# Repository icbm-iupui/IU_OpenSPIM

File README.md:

12/6/16. Additions by Indiana University, Indiana Center for Biological Microscopy
Seth Winfree completed 2015.

This repo contains the IU-OpenSPIM additions made to support NEOS AOTF control 
and filterwheel control on the emission from within the plugin.  These are supported
in the multiview acquisition tab and via a new DAC slider control for setting AOTF
transmission and filterwheel position.

This repo was orginally forked in 2015 with the intention of pulling it back to
the master but in the time I forked it and made my changes, significant changes
were made to the master making it difficult to merge.  Thus, for now, this is record
of the changes that could be implemented in the current OpenSPIM plugin to 
support an AOTF and FW from within the plugin.  

# Original README

The [OpenSPIM](http://openspim.org/) project is a collaboration between multiple
labs to establish an accessible, easily adjustable light sheet microscope
system.

The *SPIMAcquisition* plugin for [Micro Manager](https://micro-manager.org) is
the primary means to acquire image stacks with the OpenSPIM setups.

# How to build

To build this plugin, two extra steps are required before letting Maven (or
any Integrated Development Environment with a Maven integration) build the
project: The Micro-Manager artifacts need to be installed locally because they
are not available via any public Maven repository yet.

Assuming that you already have a nightly build (e.g. by following the
[Micro-Manager-dev update site](http://sites.imagej.net/Micro-Manager-dev/)),
install the artifacts into your local Maven repository by executing the
following two commands inside the `ImageJ.app/` directory containing
Micro-Manager:

```bash
cd plugins/Micro-Manager
mvn install:install-file -DgroupId=org.micromanager -Dversion=1.4.21-SNAPSHOT \
	-Dpackaging=jar -DartifactId=MMJ_ -Dfile=MMJ_.jar
mvn install:install-file -DgroupId=org.micromanager -Dversion=1.4.21-SNAPSHOT \
	-Dpackaging=jar -DartifactId=MMCoreJ -Dfile=MMCoreJ.jar
```

After that, a simple `mvn -Dscijava.enforce.skip` will build the
`SPIMAcquisition` plugin which can then be installed by copying
`target/SPIMAcquisition-<version>.jar` into `Fiji.app/mmplugins/`.

# Installing into a Micro-Manager directory instead of Fiji

The SPIMAcquisition plugin depends on a couple of components that are shipped
with Fiji but not with Micro-Manager. Therefore, you will have to work a little
harder if you want to install the plugin into a vanilla Micro-Manager as
downloaded from [the Micro-Manager website](https://micro-manager.org):

1. Run `mvn dependency:copy-dependencies` in the SPIMAcquisition directory
2. From `target/dependency/` in that subdirectory, copy the `imglib2-*.jar` files to your Micro-Manager's `mmplugins/` subdirectory.
3. Copy `target/SPIMAcquisition-1.0.0-SNAPSHOT.jar` to the `mmplugins/` subdirectory, too.
4. Restart Micro-Manager.

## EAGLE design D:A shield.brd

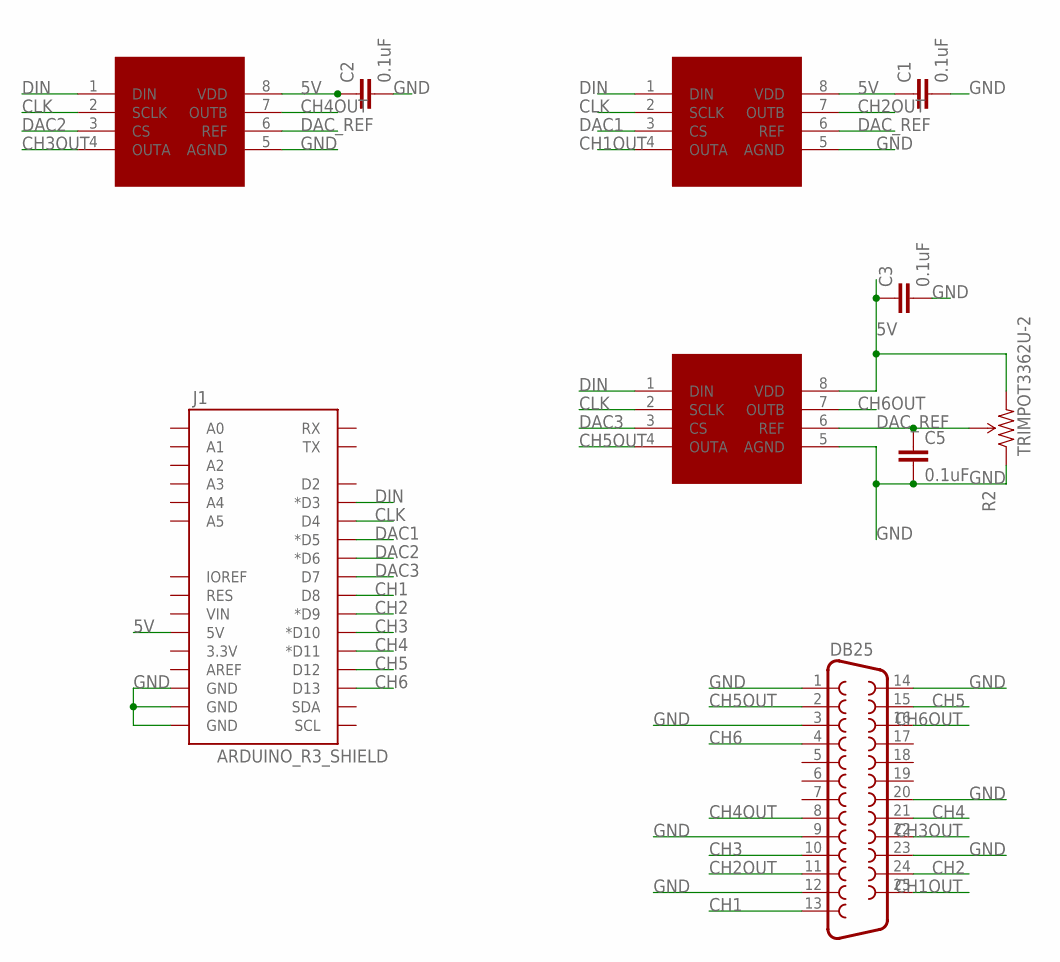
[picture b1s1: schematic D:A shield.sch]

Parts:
C1, C2, C3, C5: 0.1uF; 1206
DAC1, DAC2, DAC3: TLV5618; DIL08
DB25: F25HP
J1: ARDUINO_R3_SHIELD; UNO_R3_SHIELD
R2: TRIMPOT3362U-2; 3362U-2

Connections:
5V: C1.1, C2.1, C3.1, DAC1.8 (VDD), DAC2.8 (VDD), DAC3.8 (VDD), J1.5V, R2.3 (CW)
CH1: DB25.13, J1.D8
CH1OUT: DAC1.4 (OUTA), DB25.25
CH2: DB25.24, J1.D9 (*D9)
CH2OUT: DAC1.7 (OUTB), DB25.11
CH3: DB25.10, J1.D10 (*D10)
CH3OUT: DAC3.4 (OUTA), DB25.22
CH4: DB25.21, J1.D11 (*D11)
CH4OUT: DAC3.7 (OUTB), DB25.8
CH5: DB25.15, J1.D12
CH5OUT: DAC2.4 (OUTA), DB25.2
CH6: DB25.4, J1.D13
CH6OUT: DAC2.7 (OUTB), DB25.16
CLK: DAC1.2 (SCLK), DAC2.2 (SCLK), DAC3.2 (SCLK), J1.D4
DAC1: DAC1.3 (CS), J1.D5 (*D5)
DAC2: DAC3.3 (CS), J1.D6 (*D6)
DAC3: DAC2.3 (CS), J1.D7
DAC_REF: C5.1, DAC1.6 (REF), DAC2.6 (REF), DAC3.6 (REF), R2.2 (WIPER)
DIN: DAC1.1 (DIN), DAC2.1 (DIN), DAC3.1 (DIN), J1.D3 (*D3)
GND: C1.2, C2.2, C3.2, C5.2, DAC1.5 (AGND), DAC2.5 (AGND), DAC3.5 (AGND), DB25.1, DB25.3, DB25.9, DB25.12, DB25.14, DB25.20, DB25.23, J1.GND@0 (GND), J1.GND@1 (GND), J1.GND@2 (GND), R2.1 (CCW)

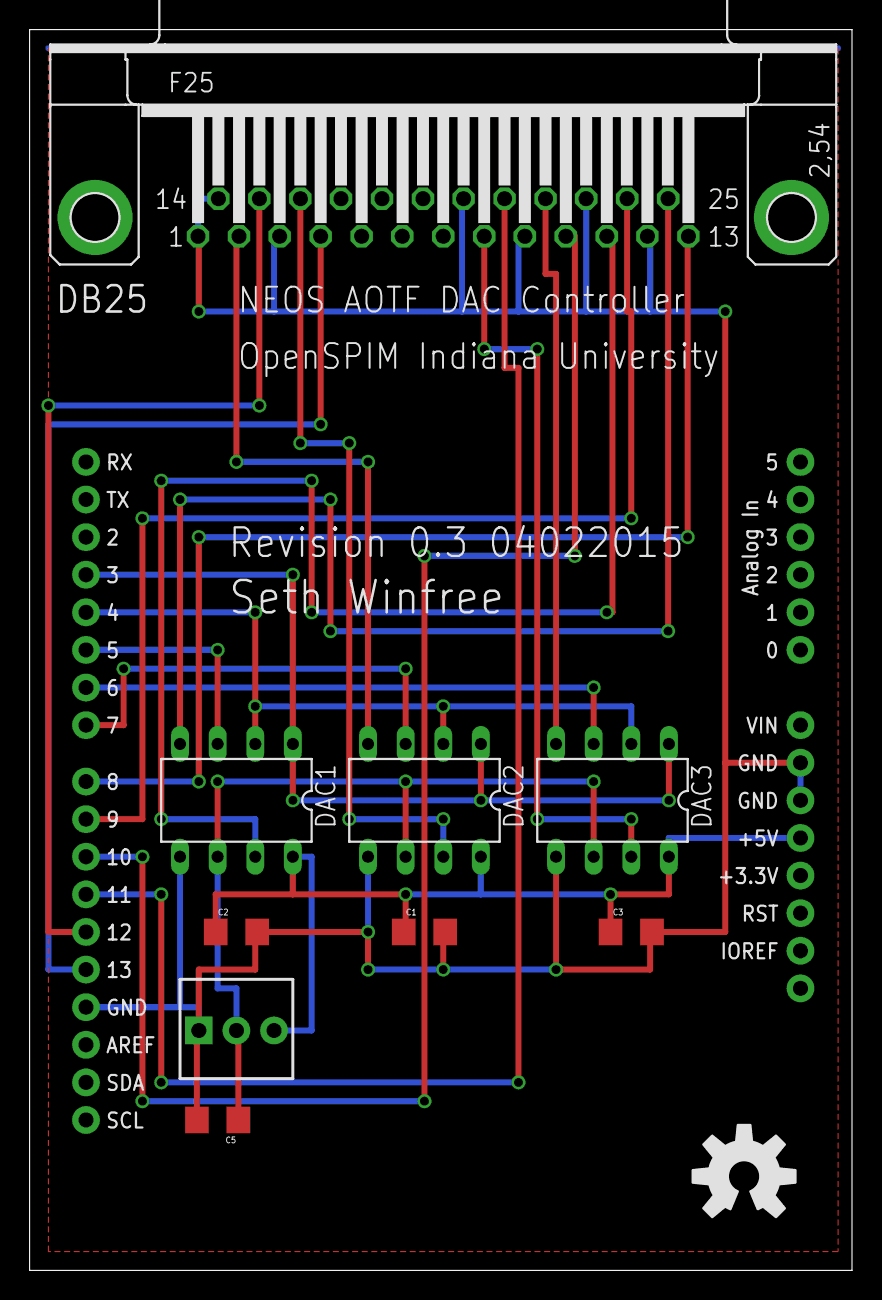
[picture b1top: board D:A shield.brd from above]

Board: 2 copper layers, 55.5 x 83.8 mm, 11 parts (0 on the bottom side), 20 nets.

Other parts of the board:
U$1: OSHW-LOGO-L

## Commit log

2016-12-06 Adding SNAPSHOT jar and firmwares
    SNAPSHOT jar supporting the arduino DAC and filterwheel within the plugin, dll for arduino in micromanager (replaces) and three arduino firmwares for the DAC, control of a neutral density filter whee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
2016-12-06 Eagle PCB design files
    These files include the corrected shield design with all the channel grounds connected correctly. Happy soldering!

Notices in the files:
parts and their libraries:
SparkFun-Boards: Licensing: CC v3.0 Share-Alike You are welcome to use this library for commercial purposes.
SparkFun-Connectors: Licensing: Creative Commons ShareAlike 4.0 International - https://creativecommons.org/licenses/by-sa/4.0
